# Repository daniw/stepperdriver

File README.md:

stepperdriver
=============

Simple stepper motor drive using L297 and L298 from ST Microelectronics

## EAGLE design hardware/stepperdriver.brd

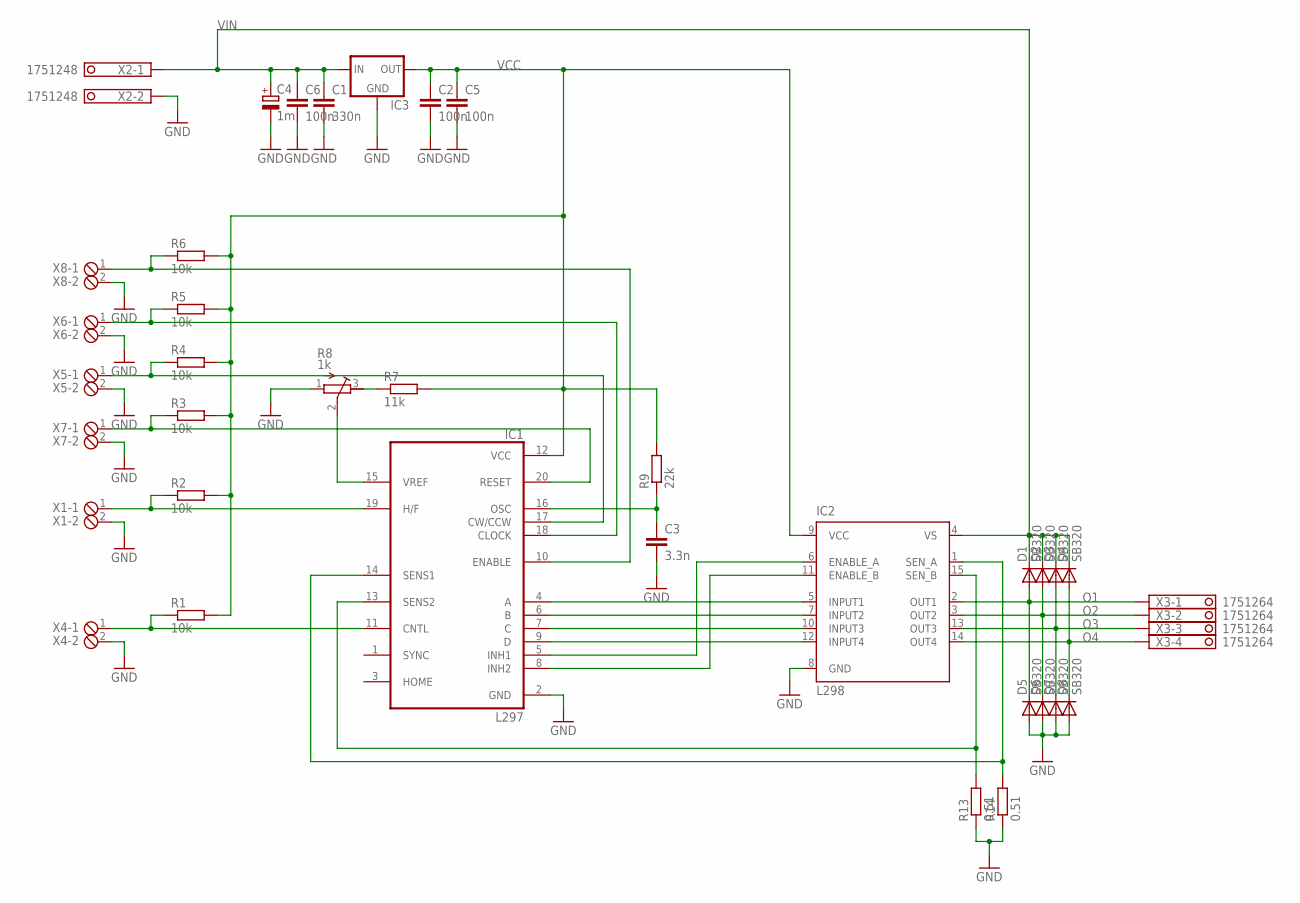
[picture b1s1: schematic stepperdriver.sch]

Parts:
C1: 330n; C050-035X075
C2, C5, C6: 100n; C050-035X075
C3: 3.3n; C050-035X075
C4: 1m; E5-13
D1, D2, D3, D4, D5, D6, D7, D8: SB320; DO201-15
IC1: L297; DIL20
IC2: L298; MULTIWATT-15
IC3: 78XXS
R1, R2, R3, R4, R5, R6: 10k; 0207/10
R7: 11k; 0207/10
R8: 1k; RTRIM64W
R9: 22k; 0207/10
R13, R14: 0.51; 0411/15
X1, X4, X5, X6, X7, X8: MPT2; 2POL254
X2: 1751248
X3: 1751264

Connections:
GND: C1.2, C2.2, C3.2, C4.-, C5.2, C6.2, D5.A, D6.A, D7.A, D8.A, IC1.2 (GND), IC2.8 (GND), IC3.GND, R8.1 (E), R13.1, R14.1, X1.2, X2.2, X4.2, X5.2, X6.2, X7.2, X8.2
unnamed: IC1.9 (D), IC2.12 (INPUT4)
unnamed: IC1.7 (C), IC2.10 (INPUT3)
unnamed: IC1.5 (INH1), IC2.6 (ENABLE_A)
unnamed: IC1.8 (INH2), IC2.11 (ENABLE_B)
unnamed: IC1.6 (B), IC2.7 (INPUT2)
unnamed: IC1.4 (A), IC2.5 (INPUT1)
unnamed: IC1.13 (SENS2), IC2.15 (SEN_B), R13.2
unnamed: IC1.14 (SENS1), IC2.1 (SEN_A), R14.2
unnamed: C3.1, IC1.16 (OSC), R9.1
unnamed: IC1.19 (H/F), R2.1, X1.1
unnamed: IC1.10 (ENABLE), R6.1, X8.1
unnamed: IC1.11 (CNTL), R1.1, X4.1
unnamed: IC1.17 (CW/CCW), R4.1, X5.1
unnamed: IC1.18 (CLOCK), R5.1, X6.1
unnamed: IC1.20 (RESET), R3.1, X7.1
unnamed: R7.1, R8.3 (A)
unnamed: IC1.15 (VREF), R8.2 (S)
O1: D1.A, D5.C, IC2.2 (OUT1), X3.1
O2: D2.A, D6.C, IC2.3 (OUT2), X3.2
O3: D3.A, D7.C, IC2.13 (OUT3), X3.3
O4: D4.A, D8.C, IC2.14 (OUT4), X3.4
VCC: C2.1, C5.1, IC1.12 (VCC), IC2.9 (VCC), IC3.OUT, R1.2, R2.2, R3.2, R4.2, R5.2, R6.2, R7.2, R9.2
VIN: C1.1, C4.+, C6.1, D1.C, D2.C, D3.C, D4.C, IC2.4 (VS), IC3.IN, X2.1

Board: 2 copper layers, 36 parts (0 on the bottom side), 24 nets, no tracks yet.

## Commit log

2013-10-18 Schema
2013-10-18 PCB, Bauteile noch nicht platziert
2013-10-18 PDF des aktuellen Standes
2013-10-18 PDF nicht mehr gespiegelt
2013-10-19 .gitignore erstellt
2013-10-19 Shuntwiderstände auf 2 Stück reduziert
2013-10-19 Bauteile grob platziert
2013-10-19 Bauteile platziert
2014-06-08 Datenblätter für einige Schrittmotortreiber
2014-07-11 Treiber mit L297 und L298 in Ordner l297 verschoben
2014-09-28 First work on stepperdriver
